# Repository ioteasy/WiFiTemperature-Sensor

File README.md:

# WiFiTemperature-Sensor
WiFi Temperature sensor based on ESP8266

## Support sensores:
DHT22/DHT11

SHT21D

Si7021

DS18B20

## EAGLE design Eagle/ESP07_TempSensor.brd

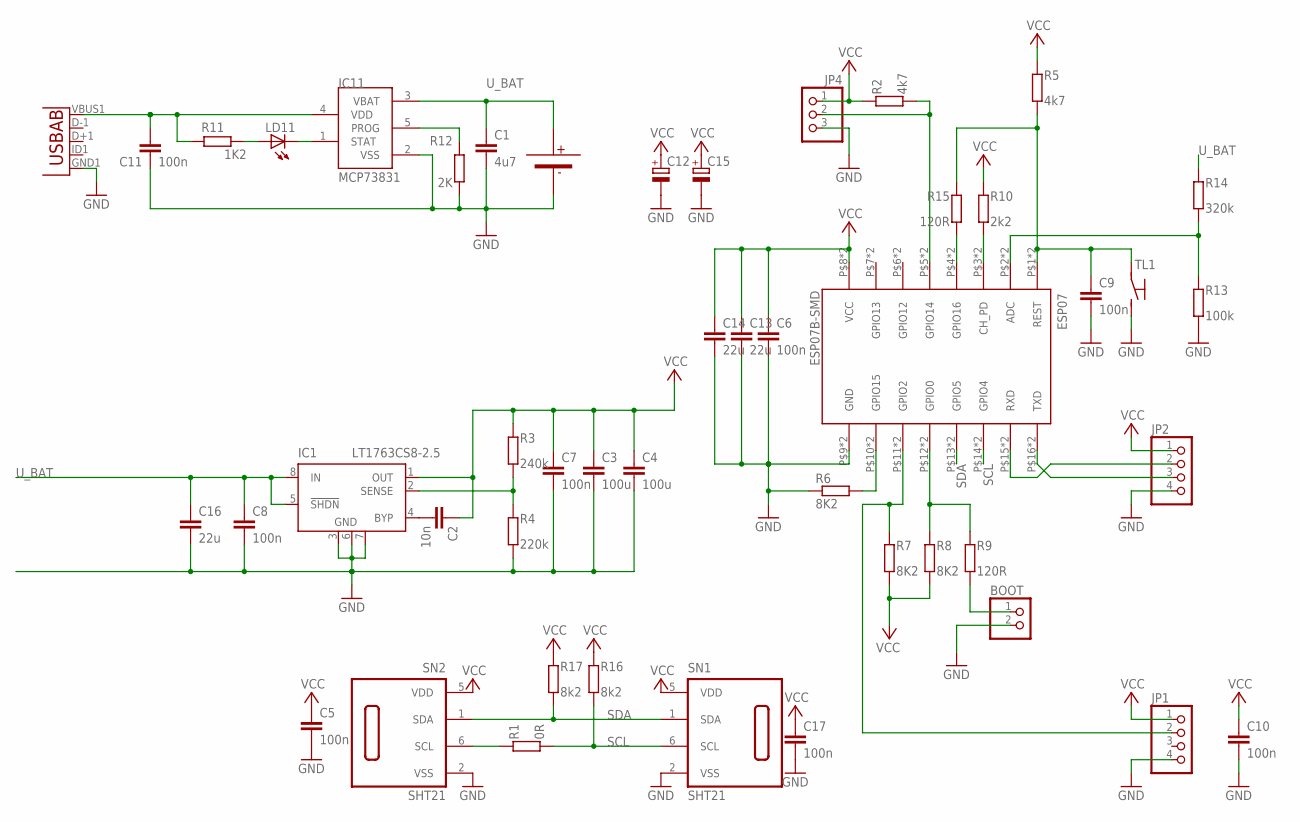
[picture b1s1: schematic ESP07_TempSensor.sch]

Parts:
BOOT: PINHD-1X2; 1X02
C1: 4u7; C0805
C2: 10n; C0805
C3, C4: 100u; C1206
C5, C6, C8, C9, C10, C11, C17: 100n; C0805
C7: 100n; C1206
C12, C15: CPOL-EUSMCC; SMC_C
C13, C14, C16: 22u; C0805
ESP07: ESP07B-SMD; ESP07
IC1: LT1763CS8-2.5; SOIC8
IC11: MCP73831; SOT23-5L
JP1, JP2: PINHD-1X4; 1X04
JP4: PINHD-1X3; 1X03
LD11: LEDCHIPLED_0805; CHIPLED_0805
R1: 0R; M0805
R2, R5: 4k7; M0805
R3: 240k; M0805
R4: 220k; M0805
R6, R7, R8: 8K2; M0805
R9, R15: 120R; M0805
R10: 2k2; M0805
R11: 1K2; M0805
R12: 2K; M0805
R13: 100k; M0805
R14: 320k; M0805
R16, R17: 8k2; M0805
SN1, SN2: SHT21; DFN6/SHT
TL1: TS1107GS
U1: USB""; USB-MICRO-SMD
U$2: 18650_CLIPS; CLIPS_18650

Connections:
FB: IC1.2 (SENSE), R3.1, R4.2
GND: BOOT.2, C1.2, C3.2, C4.2, C5.2, C6.2, C7.2, C8.2, C9.2, C10.2, C11.1, C12.-, C13.2, C14.2, C15.-, C16.2, C17.2, ESP07.P9 (GND), ESP07.P$9 (GND), IC1.3 (GND), IC1.6 (GND), IC1.7 (GND), IC11.2 (VSS), JP1.4, JP2.4, JP4.3, R4.1, R6.1, R12.1, R13.1, SN1.2 (VSS), SN2.2 (VSS), TL1.P$2 (S), U1.GND1 (GND), U$2.P$3, U$2.P$4
unnamed: C2.2, IC1.4 (BYP)
unnamed: IC11.1 (STAT), LD11.C
unnamed: ESP07.P5 (GPIO14), ESP07.P$5 (GPIO14), JP4.2, R2.1
unnamed: LD11.A, R11.1
unnamed: ESP07.P10 (GPIO15), ESP07.P$10 (GPIO15), R6.2
unnamed: R1.2, SN2.6 (SCL)
unnamed: ESP07.P12 (GPIO0), ESP07.P$12 (GPIO0), R8.2, R9.1
unnamed: IC11.5 (PROG), R12.2
unnamed: ESP07.P3 (CH_PD), ESP07.P$3 (CH_PD), R10.1
unnamed: BOOT.1, R9.2
unnamed: ESP07.P2 (ADC), ESP07.P$2 (ADC), R13.2, R14.1
unnamed: ESP07.P4 (GPIO16), ESP07.P$4 (GPIO16), R15.2
unnamed: C9.1, ESP07.P1 (REST), ESP07.P$1 (REST), R5.1, R15.1, TL1.P$1
RXD: ESP07.P15 (RXD), ESP07.P$15 (RXD), JP2.2
SCL: ESP07.P14 (GPIO4), ESP07.P$14 (GPIO4), R1.1, R16.1, SN1.6 (SCL)
SDA: ESP07.P13 (GPIO5), ESP07.P$13 (GPIO5), R17.1, SN1.1 (SDA), SN2.1 (SDA)
TMP_DATA: ESP07.P11 (GPIO2), ESP07.P$11 (GPIO2), JP1.2, R7.2
TXD: ESP07.P16 (TXD), ESP07.P$16 (TXD), JP2.3
U_BAT: C1.1, C8.1, C16.1, IC1.5 (!SHDN), IC1.8 (IN), IC11.3 (VBAT), R14.2, U$2.P$1, U$2.P$2
U_CHRG: C11.2, IC11.4 (VDD), R11.2, U1.VBUS1 (VBUS)
VCC: C2.1, C3.1, C4.1, C5.1, C6.1, C7.1, C10.1, C12.+, C13.1, C14.1, C15.+, C17.1, ESP07.P8 (VCC), ESP07.P$8 (VCC), IC1.1 (OUT), JP1.1, JP2.1, JP4.1, R2.2, R3.2, R5.2, R7.1, R8.1, R10.2, R16.2, R17.2, SN1.5 (VDD), SN2.5 (VDD)

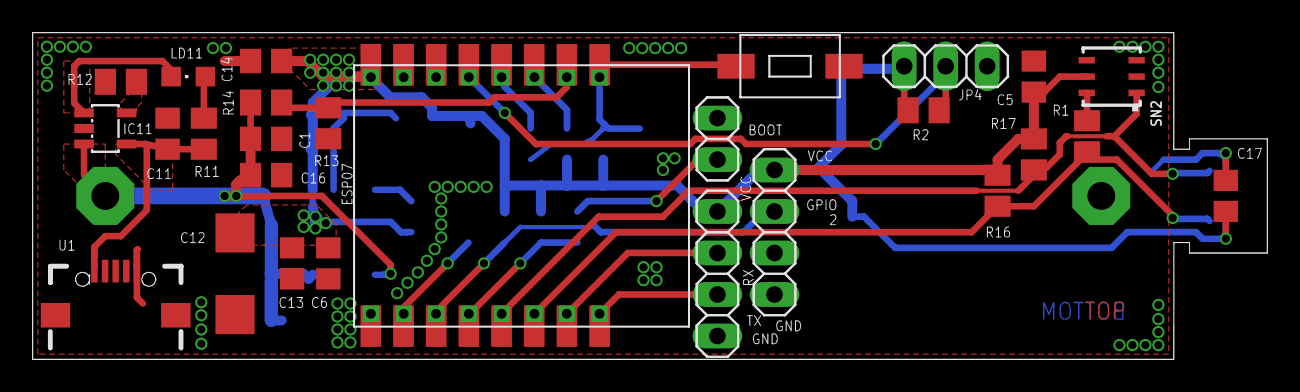
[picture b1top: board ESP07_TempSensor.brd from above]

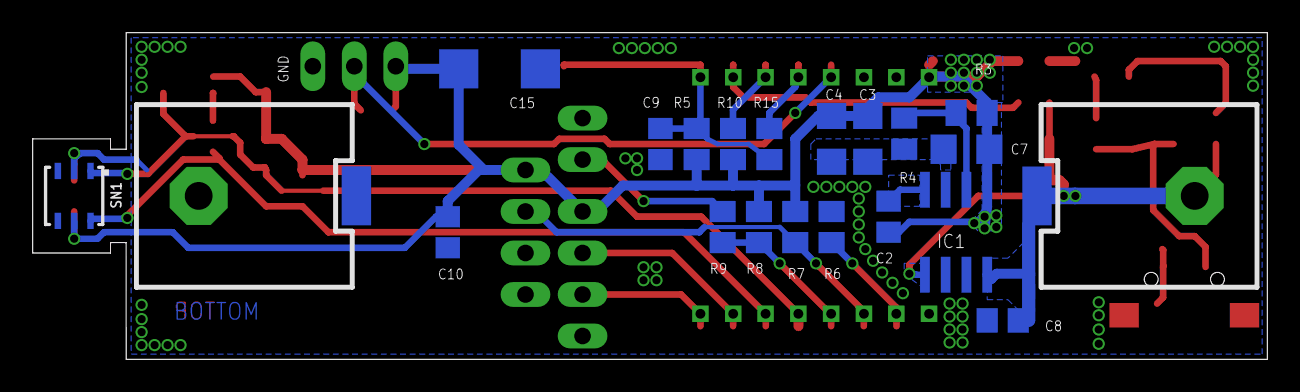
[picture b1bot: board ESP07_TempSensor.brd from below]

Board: 2 copper layers, 75.6 x 20.0 mm, 47 parts (20 on the bottom side), 23 nets.

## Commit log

2018-05-03 add files
2018-05-21 add files to Software
2018-05-21 readme
2018-05-22 add schematic and Gerber Data
2018-05-22 add pcb
2018-05-22 add image with SHT21

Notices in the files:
parts and their libraries:
sensirion: Copyright (C) 2011, Bob Starr
